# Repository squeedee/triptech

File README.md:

# Triptech

## Author

Rasheed Abdul-Aziz

## Description

Three-channel filtered gate effect for Daisy Pod. Stereo audio input is split into three parallel
filter channels, each with its own gate driven by an AD envelope. A 16-step sequencer opens the
gates rhythmically, clocked from MIDI or an internal clock. All parameters are controlled via MIDI
CC. A browser-based controller (`controller.html`) provides a full GUI with bidirectional MIDI CC
sync.

Each channel has a selectable filter type (LP / BP / HP / Notch) and slope (6 / 12 / 24 dB/oct).
Envelope amount is unipolar (0–100%) with 7-bit resolution. LFO amount is bipolar (±100%) with 14-bit resolution.

Button 1 starts and stops the sequencer. Button 2 sets the internal BPM via tap tempo.
The encoder selects patterns. Clicking the encoder toggles bypass.

## Building

```bash
git submodule update --init --recursive
make all
```

## Flashing

The app runs from the Daisy's 8 MB external **QSPI** flash (`APP_TYPE = BOOT_QSPI`),
not the 128 KB internal flash. Because the on-board micro-USB is blocked by the
menu header, flashing is done over **SWD/JTAG with an ST-Link**, not DFU:

```bash
make program             # build/triptech.elf -> QSPI (0x90040000), verify, reset
make program-bootloader  # one-time: Daisy bootloader -> internal flash (0x08000000)
```

This uses OpenOCD with the ST-Link **DAP** driver (`PGM_DEVICE = interface/stlink-dap.cfg`)
plus `daisy_qspi.cfg`, which brings up the QUADSPI and unlocks the IS25LP064A so
OpenOCD's `stmqspi` driver can write it. (The default HLA ST-Link driver makes
`stmqspi` hang — DAP mode is required.) Override the probe with
`make program PGM_DEVICE=...`.

## Clock Sources

TRS MIDI in is the authoritative clock source. USB MIDI provides clock only when no TRS clock has
been received in the last 500 ms. When neither source is active, the internal clock runs at the
BPM set by tap tempo.

MIDI Start / Stop / Continue are handled from the active clock source.

## Pod Controls

| Control       | Function                                                                                                                  |
|---------------|---------------------------------------------------------------------------------------------------------------------------|
| Button 1      | Start / stop sequencer (stop resets to step 0)                                                                            |
| Button 2      | Tap tempo — sets internal BPM from tap interval (taps > 2 s apart reset the measurement)                                 |
| Encoder click | Toggle bypass (straight-through audio)                                                                                    |
| Encoder turn  | Select pattern (wraps 0–15)                                                                                               |
| LED 1         | Gate activity: blue = Ch1, green = Ch2, red = Ch3                                                                         |
| LED 2         | Bypass: solid white. MIDI clock: solid green = running. Internal clock: red beat-pulse = running, dim red = stopped       |

## MIDI Note → Gate

NoteOn messages on MIDI channel 1 trigger channel gates directly, regardless of sequencer run state:

| Note          | MIDI # | Gate    |
|---------------|--------|---------|
| C4 (middle C) | 60     | Ch 1    |
| C#4           | 61     | Ch 2    |
| D4            | 62     | Ch 3    |

The device echoes each NoteOn back and sends NoteOff when the channel's envelope finishes.

## MIDI CC Map

### Global

| CC  | Parameter      | Range                           | Default |
|-----|----------------|---------------------------------|---------|
| 14  | Pattern select | 0–127 → patterns 0–15           | 0       |
| 15  | Run / Stop     | ≥ 64 = run, < 64 = stop         | stopped |
| 16  | LFO rate       | 0–127 → 0.1–20 Hz (log)         | 1 Hz    |
| 17  | Chance         | 0–127 → 0–100% gate probability | 100%    |
| 18  | Bypass         | ≥ 64 = bypass on, < 64 = off    | off     |
| 19  | BPM            | 0–127 → 20–300 BPM              | 120 BPM |
| 119 | State dump     | any → device sends all CC state | —       |

### Per Channel  (Ch1 base = CC 20, Ch2 base = CC 36, Ch3 base = CC 52)

| Offset | Parameter               | Range                      | Ch1 Default | Ch2 Default | Ch3 Default |
|--------|-------------------------|----------------------------|-------------|-------------|-------------|
| +0     | Cutoff                  | 100–20000 Hz (log)         | 800 Hz      | 2000 Hz     | 1200 Hz     |
| +1     | Resonance               | 0–0.95                     | 0.5         | 0.5         | 0.5         |
| +2     | Drive (pre-filter gain) | ×1–×4                      | ×1          | ×1          | ×1          |
| +3     | Env amount              | 7-bit unipolar, 0–100%     | 100%        | 100%        | 100%        |
| +4     | Attack                  | 1 ms–2 s (log)             | 5 ms        | 5 ms        | 5 ms        |
| +5     | Decay                   | 10 ms–4 s (log)            | 200 ms      | 200 ms      | 200 ms      |
| +6     | Level                   | 0–1                        | 0.7         | 0.7         | 0.7         |
| +7     | Pan                     | full left–full right       | center      | 25% L       | 25% R       |
| +8     | LFO amount MSB          | 14-bit bipolar, −1 to +1   | 0%          | 0%          | 0%          |
| +9     | Filter type             | 0=LP, 32=BP, 64=HP, 96=Notch | LP        | BP          | HP          |
| +10    | Filter slope            | 0=6 dB, 63=12 dB, 126=24 dB | 12 dB      | 12 dB       | 12 dB       |
| +12    | LFO amount LSB          | 14-bit pair with +8        | —           | —           | —           |

Offset +8/+12 forms a 14-bit pair for LFO amount (MSB sent first, then LSB).

Examples: Ch1 cutoff = CC 20, Ch2 pan = CC 43, Ch3 LFO amount = CC 60.

## MIDI Feedback (Bidirectional Sync)

The device sends CC back on both TRS and USB MIDI whenever state changes via physical controls:

| Physical control | CC | Value                     |
|------------------|----|---------------------------|
| Encoder turn     | 14 | pattern × 8               |
| Button 1         | 15 | 127 = run, 0 = stop       |
| Encoder click    | 18 | 127 = bypass on, 0 = off  |
| Button 2 (tap)   | 19 | BPM scaled 0–127          |

The device also sends DSP and main-loop load every 250 ms:

| CC | Parameter     | Range              |
|----|---------------|--------------------|
| 10 | DSP avg load  | 0–127 = 0–100%     |
| 11 | DSP peak load | 0–127 = 0–100%     |
| 12 | Loop avg time | 0–127 = 0–500 µs   |
| 13 | Loop peak time| 0–127 = 0–500 µs   |

Send CC 119 (any value) to request a full state dump of all parameters.

## Web Controller

Open [./desktop-controller.html](./desktop-controller.html) in a browser with Web MIDI support (Chrome / Edge). Select the Daisy as
both MIDI In and MIDI Out — the page auto-selects it on load. Click **Sync** to pull current
device state into the UI at any time.

For an emulation of the desktop module, open [expanded-controller.html](./expanded-controller.html)

### Controller Keyboard Shortcuts

| Key          | Action                        |
|--------------|-------------------------------|
| Space        | Run / Stop                    |
| B            | Bypass                        |
| 1 / 2 / 3   | Trigger Ch 1 / Ch 2 / Ch 3   |
| Shift 1/2/3  | Mute Ch 1 / Ch 2 / Ch 3      |
| Ctrl 1/2/3   | Solo Ch 1 / Ch 2 / Ch 3      |
| ?            | Show help                     |

## Patterns

Each step triggers at most one channel. Patterns marked ✦ use all three channels.

| #  | Name                                              |
|----|---------------------------------------------------|
| 0  | Open Ch1 — Ch1 every 16th                         |
| 1  | Classic — Ch1 quarters / Ch3 8th-off / Ch2 fill ✦ |
| 2  | Ch1/Ch3 alternating                               |
| 3  | Even split — Ch1 / Ch2 / Ch3 / rest cycling     ✦ |
| 4  | Ch1 first half, Ch2 second half                   |
| 5  | Quarter rotation — Ch1 / Ch2 / Ch3 / Ch1        ✦ |
| 6  | Open Ch3 — Ch3 every 16th                         |
| 7  | Ch1→Ch2→Ch3 rotation every step                 ✦ |
| 8  | Ch1 quarters + Ch2 8th-offbeats                   |
| 9  | Triplet rotation                                ✦ |
| 10 | Syncopated three-way                            ✦ |
| 11 | Channel blocks                                  ✦ |
| 12 | Clave (son 3+3+2) with Ch3 fills and Ch2 sparse ✦ |
| 13 | Half-time sparse                                ✦ |
| 14 | Dotted-8th Ch1 + Ch3 fills                        |
| 15 | Complex syncopated                              ✦ |

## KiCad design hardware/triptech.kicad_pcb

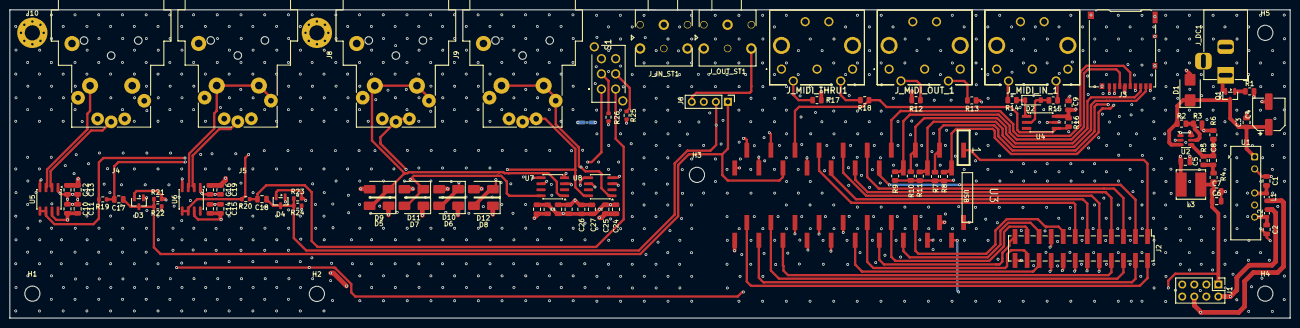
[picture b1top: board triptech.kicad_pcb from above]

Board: 4 copper layers, 270.0 x 65.0 mm, 101 parts (1 on the bottom side), 74 nets.

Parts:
C1, C2, C10, C12, C14, C16, C17, C18, C20, C22, C24, C26: 10u; C_0805_2012Metric
C3, C5, C9, C11, C13, C15, C19, C21, C23, C25, C27: 100n; C_0805_2012Metric
C4: 100u/25V; CP_Elec_6.3x7.7
C6, C7: 22u; C_0805_2012Metric
C8: 75pf; C_0805_2012Metric
D1: SMBJ15A; D_SMB
D2: 1N4148W; D_SOD-123
D3, D4: BAT54S; SOT-23
D5, D6, D7, D8, D9, D10, D11, D12: SM4004; D_SMA
H1, H2, H3, H4, H5: MountingHole; MountingHole_3.2mm_M3
H3#2: MountingHole_M3; MountingHole_3.2mm_M3_Pad_Via
J1: Power; PinHeader_2x04_P2.54mm_Vertical
J2: GPIO Header; PinHeader_2x12_P2.54mm_Vertical_SMD
J3: Micro_SD_Card; microSD_HC_Hirose_DM3AT-SF-PEJM5
J4, J5, J8, J9: NCJ6FA-H-0; Jack_XLR-6.35mm_Neutrik_NCJ6FA-H-0_Horizontal
J6: Conn_01x04_Pin; PinHeader_1x04_P2.54mm_Vertical
J7, J10: Earth; MountingHole_3.2mm_M3_Pad_Via
JP1: Earth-Gnd Disconnect; SolderJumper-2_P1.3mm_Bridged_Pad1.0x1.5mm
J_DC1: Barrel_Jack_2.1mm; BarrelJack_Horizontal
J_IN_ST1: STX-3100-3CB; Jack_3.5mm_Kycon_STX-3100-3CB
J_MIDI_IN_1: SDS-50J; SDS50J
J_MIDI_OUT_1: SDS-50J; SDS50J
J_MIDI_THRU1: SDS-50J; SDS50J
J_OUT_ST1: STX-3100-3CB; Jack_3.5mm_Kycon_STX-3100-3CB
L1, L2: BLM18PG121SN1; L_0603_1608Metric
L3: 10uH; L_Bourns_SRN6045TA
Q1: SI2301CDS-T1-GE3; SOT-23
R1: 10k; R_0805_2012Metric
R2: 100k; R_0805_2012Metric
R3: 13.7k; R_0805_2012Metric
R4: 49.9R; R_0805_2012Metric
R5: 100k 1%; R_0805_2012Metric
R6: 13.3k 1%; R_0805_2012Metric
R7, R8, R9, R10, R11: 47K; R_0805_2012Metric
R12, R17, R18: 33R; R_0805_2012Metric
R13: 10R; R_0805_2012Metric
R14, R15: 220R; R_0805_2012Metric
R16: 270R; R_0805_2012Metric
R19, R20: 1.2k; R_0603_1608Metric
R21, R22, R23, R24: 100k; R_0603_1608Metric
R25, R26: 120R; R_0603_1608Metric
S1: LC2255EESP
U1: TMA-1212D; Converter_DCDC_TRACO_TMA-05xxD_12xxD_Dual_THT
U2: TPS54302; SOT-23-6
U3: Daisy_Seed; DAISY_SEED_SMT
U4: H11L1SM; SO-6_4.4x3.6mm_P1.27mm
U5, U6: THAT1246; SOIC-8_3.9x4.9mm_P1.27mm
U7, U8: THAT1646; SOIC-8_3.9x4.9mm_P1.27mm

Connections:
+3V3A: J1.8, U3.21 (3V3_A)
+3V3D: C9.1, J1.7, J3.4 (VDD), R7.1, R8.1, R9.1, R10.1, R11.1, R12.1, R16.1, R17.1, U3.38 (3V3_D), U4.6
+5V: C6.1, C7.1, D3.2 (K), D4.2 (K), J1.1, L3.2, R4.1, R21.2, R23.2, U3.39 (VIN)
+12VA: C10.1, C11.1, C14.1, C15.1, C20.1, C21.1, C24.1, C25.1, D5.1 (K), D6.1 (K), D7.1 (K), D8.1 (K), J1.2, L2.2, U5.7 (Vcc/V+), U6.7 (Vcc/V+), U7.6 (Vcc/V+), U8.6 (Vcc/V+)
+12V_RAW: C3.1, C4.1, D1.1 (A1), Q1.3 (D), R2.1, U1.1 (+Vin), U2.3 (VIN)
-12VA: C12.2, C13.2, C16.2, C19.2, C22.2, C23.2, C26.2, C27.2, D9.2 (A), D10.2 (A), D11.2 (A), D12.2 (A), J1.6, L1.2, U5.4 (Vee/V-), U6.4 (Vee/V-), U7.5 (Vee/V-), U8.5 (Vee/V-)
/Power/+12V_IN: J_DC1.1, Q1.2 (S)
AUDIO_IN_L: C17.2, D3.3 (COM), J6.1, R21.1, R22.2, U3.16 (AUDIO_IN_1)
AUDIO_IN_R: C18.2, D4.3 (COM), J6.2, R23.1, R24.2, U3.17 (AUDIO_IN_2)
AUDIO_OUT_L: J6.3, J_OUT_ST1.2 (T), U3.18 (AUDIO_OUT_1), U7.4 (In)
AUDIO_OUT_R: J6.4, J_OUT_ST1.5 (R), U3.19 (AUDIO_OUT_2), U8.4 (In)
Earth: J4.1, J4.G, J4.S, J5.1, J5.G, J5.S, J7.1, J8.1, J8.G, J8.S, J9.1, J9.G, J9.S, J10.1, JP1.2 (B)
GND: C1.2, C2.2, C3.2, C4.2, C6.2, C7.2, C9.2, C10.2, C11.2, C12.1, C13.1, C14.2, C15.2, C16.1, C19.1, C20.2, C21.2, C22.1, C23.1, C24.2, C25.2, C26.1, C27.1, D1.2 (A2), D3.1 (A), D4.1 (A), J1.3, J1.4, J1.5, J2.24, J3.6 (VSS), J3.9 (GND), J3.10 (Detect), J3.11 (SHIELD), JP1.1 (A), J_DC1.2, J_IN_ST1.1 (S), J_MIDI_IN_1.2, J_MIDI_IN_1.MH1, J_MIDI_IN_1.MH2, J_MIDI_IN_1.MH3, J_MIDI_IN_1.MH4, J_MIDI_OUT_1.2, J_MIDI_OUT_1.MH1, J_MIDI_OUT_1.MH2, J_MIDI_OUT_1.MH3, J_MIDI_OUT_1.MH4, J_MIDI_THRU1.2, J_MIDI_THRU1.MH1, J_MIDI_THRU1.MH2, J_MIDI_THRU1.MH3, J_MIDI_THRU1.MH4, J_OUT_ST1.1 (S), R1.2, R3.2, R6.2, R22.1, R24.1, R25.2, R26.2, S1.MH1, S1.MH2, U1.2 (-Vin), U1.5 (Com), U2.1 (GND), U3.20 (AGND), U3.40 (DGND), U4.5, U5.1 (Ref), U6.1 (Ref), U7.3 (Gnd), U8.3 (Gnd)
GPIO_D0: J2.1, U3.1 (D0)
GPIO_D7: J2.3, U3.8 (D7)
GPIO_D8: J2.5, U3.9 (D8)
GPIO_D9: J2.7, U3.10 (D9)
GPIO_D10: J2.9, U3.11 (D10)
GPIO_D11: J2.11, U3.12 (D11)
GPIO_D12: J2.13, U3.13 (D12)
GPIO_D15: J2.2, U3.22 (D15)
GPIO_D16: J2.4, U3.23 (D16)
GPIO_D17: J2.6, U3.24 (D17)
GPIO_D18: J2.8, U3.25 (D18)
GPIO_D19: J2.10, U3.26 (D19)
GPIO_D20: J2.12, U3.27 (D20)
GPIO_D21: J2.14, U3.28 (D21)
GPIO_D22: J2.16, U3.29 (D22)
GPIO_D23: J2.18, U3.30 (D23)
GPIO_D24: J2.20, U3.31 (D24)
GPIO_D25: J2.22, U3.32 (D25)
GPIO_D26: J2.23, U3.33 (D26)
GPIO_D27: J2.21, U3.34 (D27)
GPIO_D28: J2.19, U3.35 (D28)
GPIO_D29: J2.15, U3.36 (D29)
GPIO_D30: J2.17, U3.37 (D30)
MIDI_RX: R16.2, R18.1, U3.15 (D14), U4.4
MIDI_TX: R13.2, U3.14 (D13)
unnamed: C8.1, R4.2, R5.1
unnamed: D2.2 (A), R15.1, U4.2
unnamed: D2.1 (K), R14.1, U4.1
unnamed: D5.2 (A), D9.1 (K), J8.2, J8.T, U7.1 (Out-)
unnamed: D6.2 (A), D10.1 (K), J9.2, J9.T, U8.1 (Out-)
unnamed: D7.2 (A), D11.1 (K), J8.3, J8.R, U7.8 (Out+)
unnamed: D8.2 (A), D12.1 (K), J9.3, J9.R, U8.8 (Out+)
unnamed: J_IN_ST1.5 (R), R20.1, U6.5 (Sense), U6.6 (Vout)
unnamed: J_IN_ST1.2 (T), R19.1, U5.5 (Sense), U5.6 (Vout)
unnamed: J_MIDI_IN_1.4, R14.2
unnamed: J_MIDI_IN_1.5, R15.2
unnamed: J_MIDI_OUT_1.4, R12.2
unnamed: J_MIDI_OUT_1.5, R13.1
unnamed: J_MIDI_THRU1.4, R17.2
unnamed: J_MIDI_THRU1.5, R18.2
unnamed: Q1.1 (G), R1.1
unnamed: R26.1, S1.2 (COM_1)
unnamed: R25.1, S1.5 (COM_2)
unnamed: C17.1, R19.2, S1.1 (NO_1)
unnamed: C18.1, R20.2, S1.4 (NO_2)
unnamed: C2.1, L2.1, U1.6 (+Vout)
unnamed: C1.1, L1.1, U1.4 (-Vout)
unnamed: C5.1, U2.6 (BOOT)
unnamed: R2.2, R3.1, U2.5 (EN)
unnamed: C8.2, R5.2, R6.1, U2.4 (FB)
unnamed: C5.2, L3.1, U2.2 (SW)
unnamed: J4.2, J4.T, U5.3 (In+)
unnamed: J4.3, J4.R, U5.2 (In-)
unnamed: J5.2, J5.T, U6.3 (In+)
unnamed: J5.3, J5.R, U6.2 (In-)
SD_CK: J3.5 (CLK), U3.7 (D6)
SD_CMD: J3.3 (CMD), R9.2, U3.6 (D5)
SD_D0: J3.7 (DAT0), R10.2, U3.5 (D4)
SD_D1: J3.8 (DAT1), R11.2, U3.4 (D3)
SD_D2: J3.1 (DAT2), R7.2, U3.3 (D2)
SD_D3: J3.2 (DAT3/CD), R8.2, U3.2 (D1)

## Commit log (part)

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2026-03-06 Triptech — initial release
2026-03-06 env isn't bipolar
2026-03-06 fix clock drift
2026-03-06 refactor to have preset data in a struct
2026-03-06 Padé approximant of tanh
2026-03-06 Fix comments
2026-03-06 Switch to K+R (yay)
2026-03-07 some layout ideas
2026-03-07 better displays for type a
2026-03-07 fix delay time, update design
2026-03-07 more layout work
2026-03-08 put the lfo back dude
2026-03-08 layout also works
2026-03-08 controllers update
2026-03-08 introduce sac2k lib
2026-03-08 new design doc
2026-03-10 add a wiring configuration for a prototype controller
2026-03-10 balance in/out addenda
2026-03-14 Power Module
2026-03-14 move schematic docs out of root
2026-03-14 save patches
2026-03-14 better patterns
2026-03-14 added some amp lfoness and 1 lfo per channel
2026-03-28 Designing a pcb
2026-03-28 bunch of pdfs for lookup
2026-03-29 simulate and design proper input stage
2026-03-29 cleanup - remove unused schematics
2026-03-29 add protection circuit and repair pcb
2026-03-29 Add Pad button
2026-04-01 PCB Assembledish Design checks next
2026-04-01 Stitch WIP
2026-04-01 PCB rev 1
2026-04-01 Add Rev 1 Gerbers
2026-04-04 Validated Bom
2026-04-05 Pulled out the carrier as a project: https://github.com/squeedee/daisy-studio
2026-05-16 pattern division
2026-05-16 make the square lfo a little more trapezoid to drop clicks
2026-06-05 emulate 'menu' interface
2026-06-05 demo menu
2026-06-06 mpre menu nave
2026-06-06 soft start, color controls
2026-06-06 color saving
2026-06-06 added cpu load meters
2026-06-06 tempo updating in settings:
2026-06-06 added indicator for envelope, uv on second hidden menu
2026-06-06 add indicator of where we are in the ui
2026-06-06 mutes and solos
2026-06-06 store state for power cycle survival
2026-06-06 add reset defaults
2026-06-07 recording more state for power cycles
2026-06-07 working on bpm and glitches
2026-06-07 more midi clock fixes
2026-06-07 really fix the glitch
2026-06-07 lost of docs
2026-06-07 Carve out state
2026-06-07 carve out midi and hardware
2026-06-07 carve out the rest of the control functions
2026-06-07 limit and level shift q
2026-06-07 better mutes
2026-06-07 confirm dialog
2026-06-07 drop useless slot for sync
2026-06-26 latest ui
